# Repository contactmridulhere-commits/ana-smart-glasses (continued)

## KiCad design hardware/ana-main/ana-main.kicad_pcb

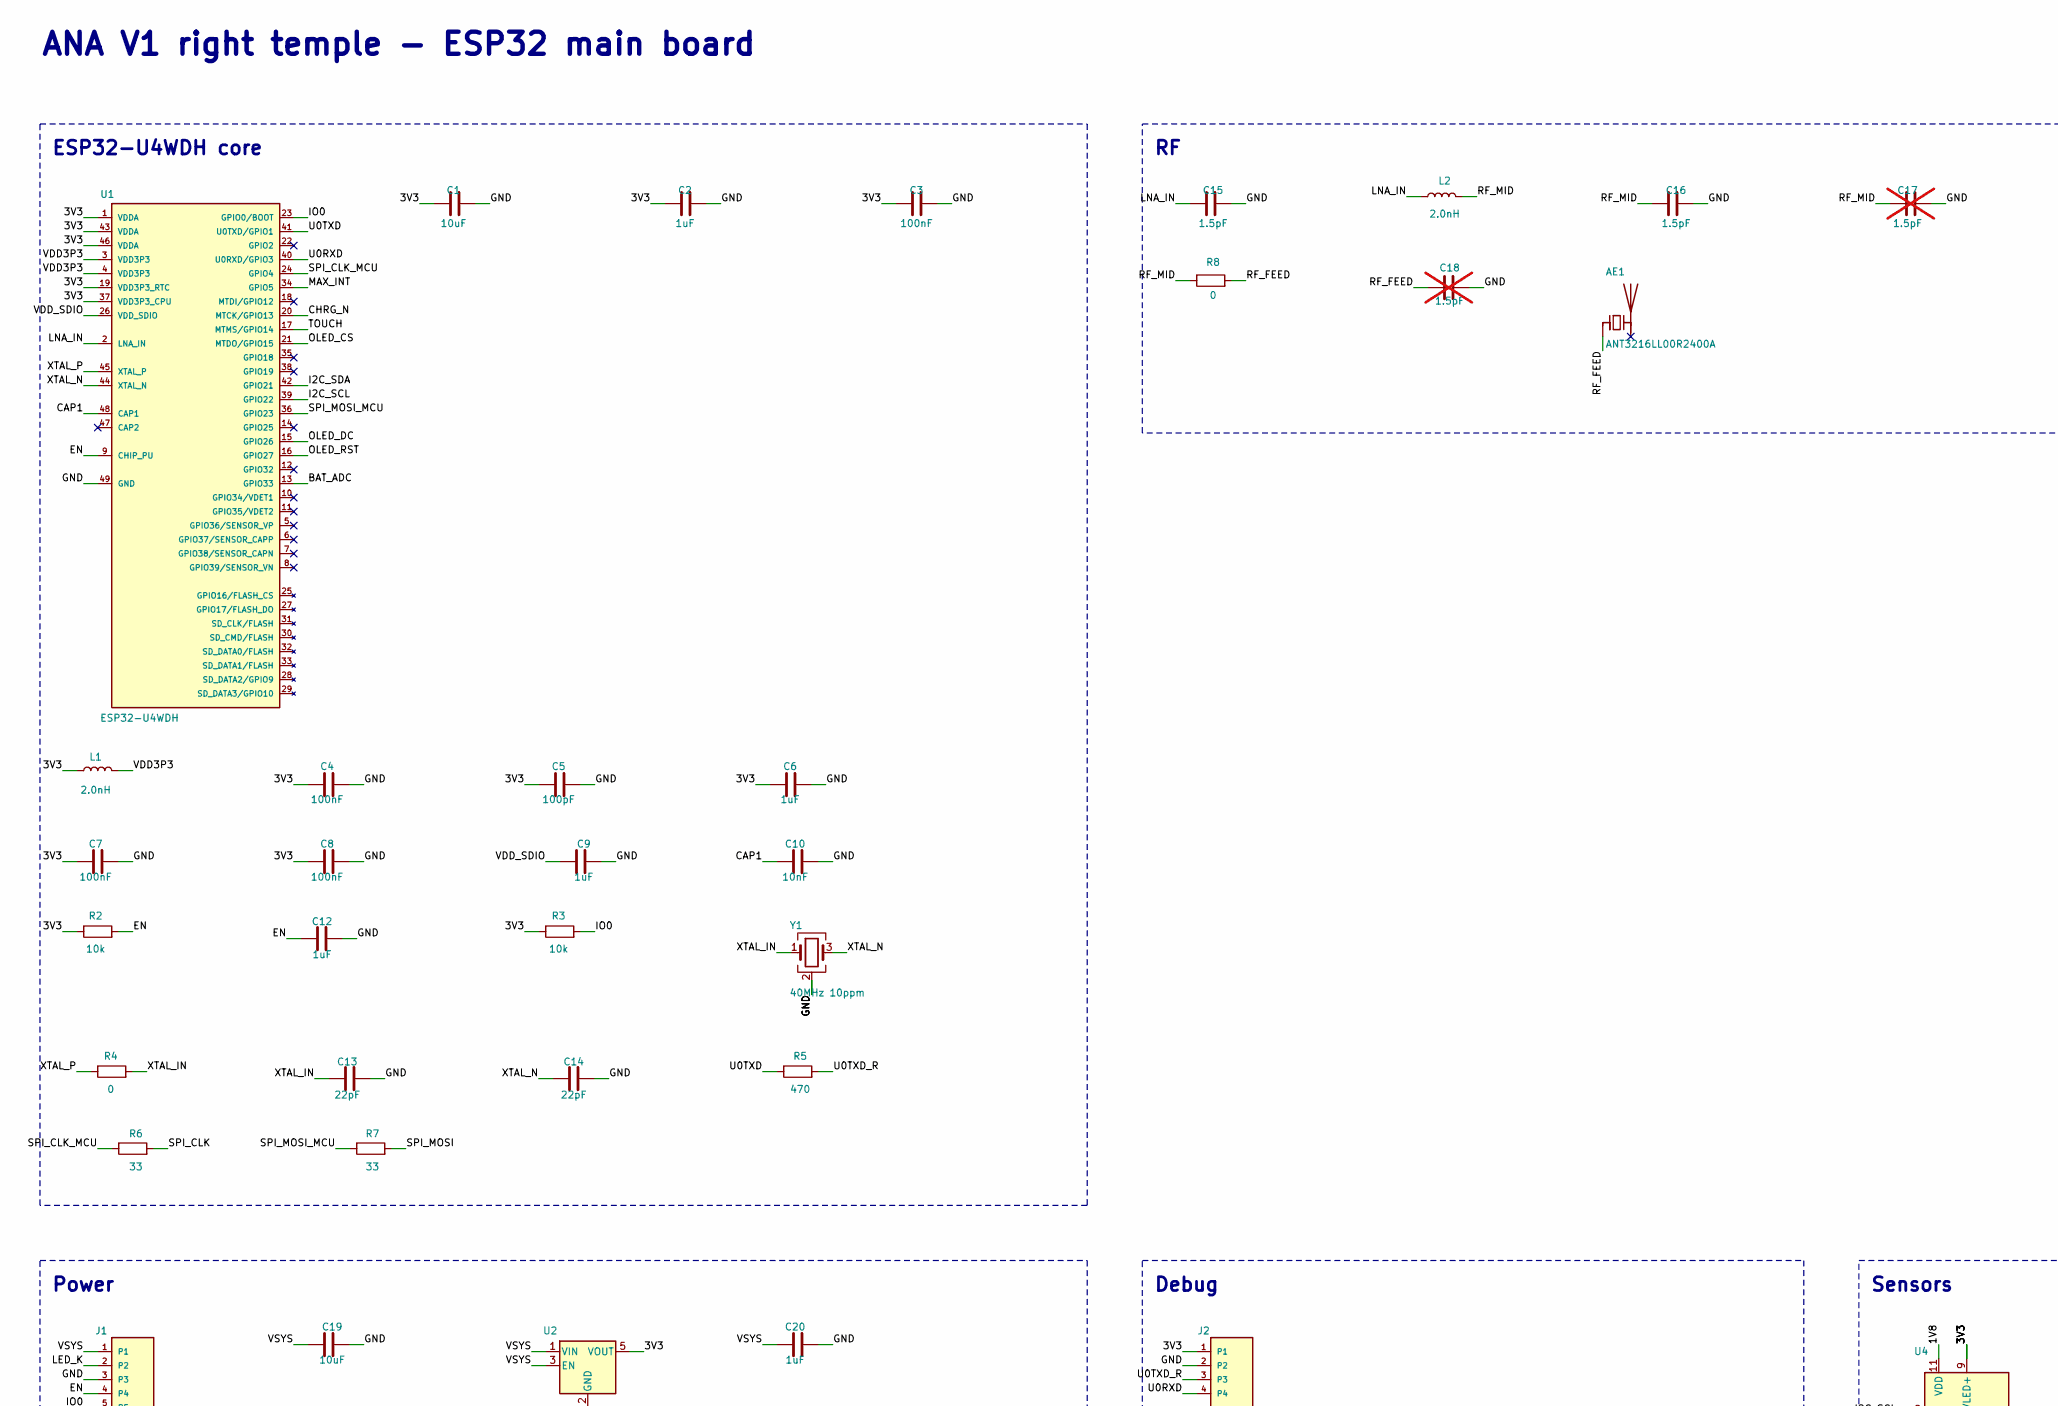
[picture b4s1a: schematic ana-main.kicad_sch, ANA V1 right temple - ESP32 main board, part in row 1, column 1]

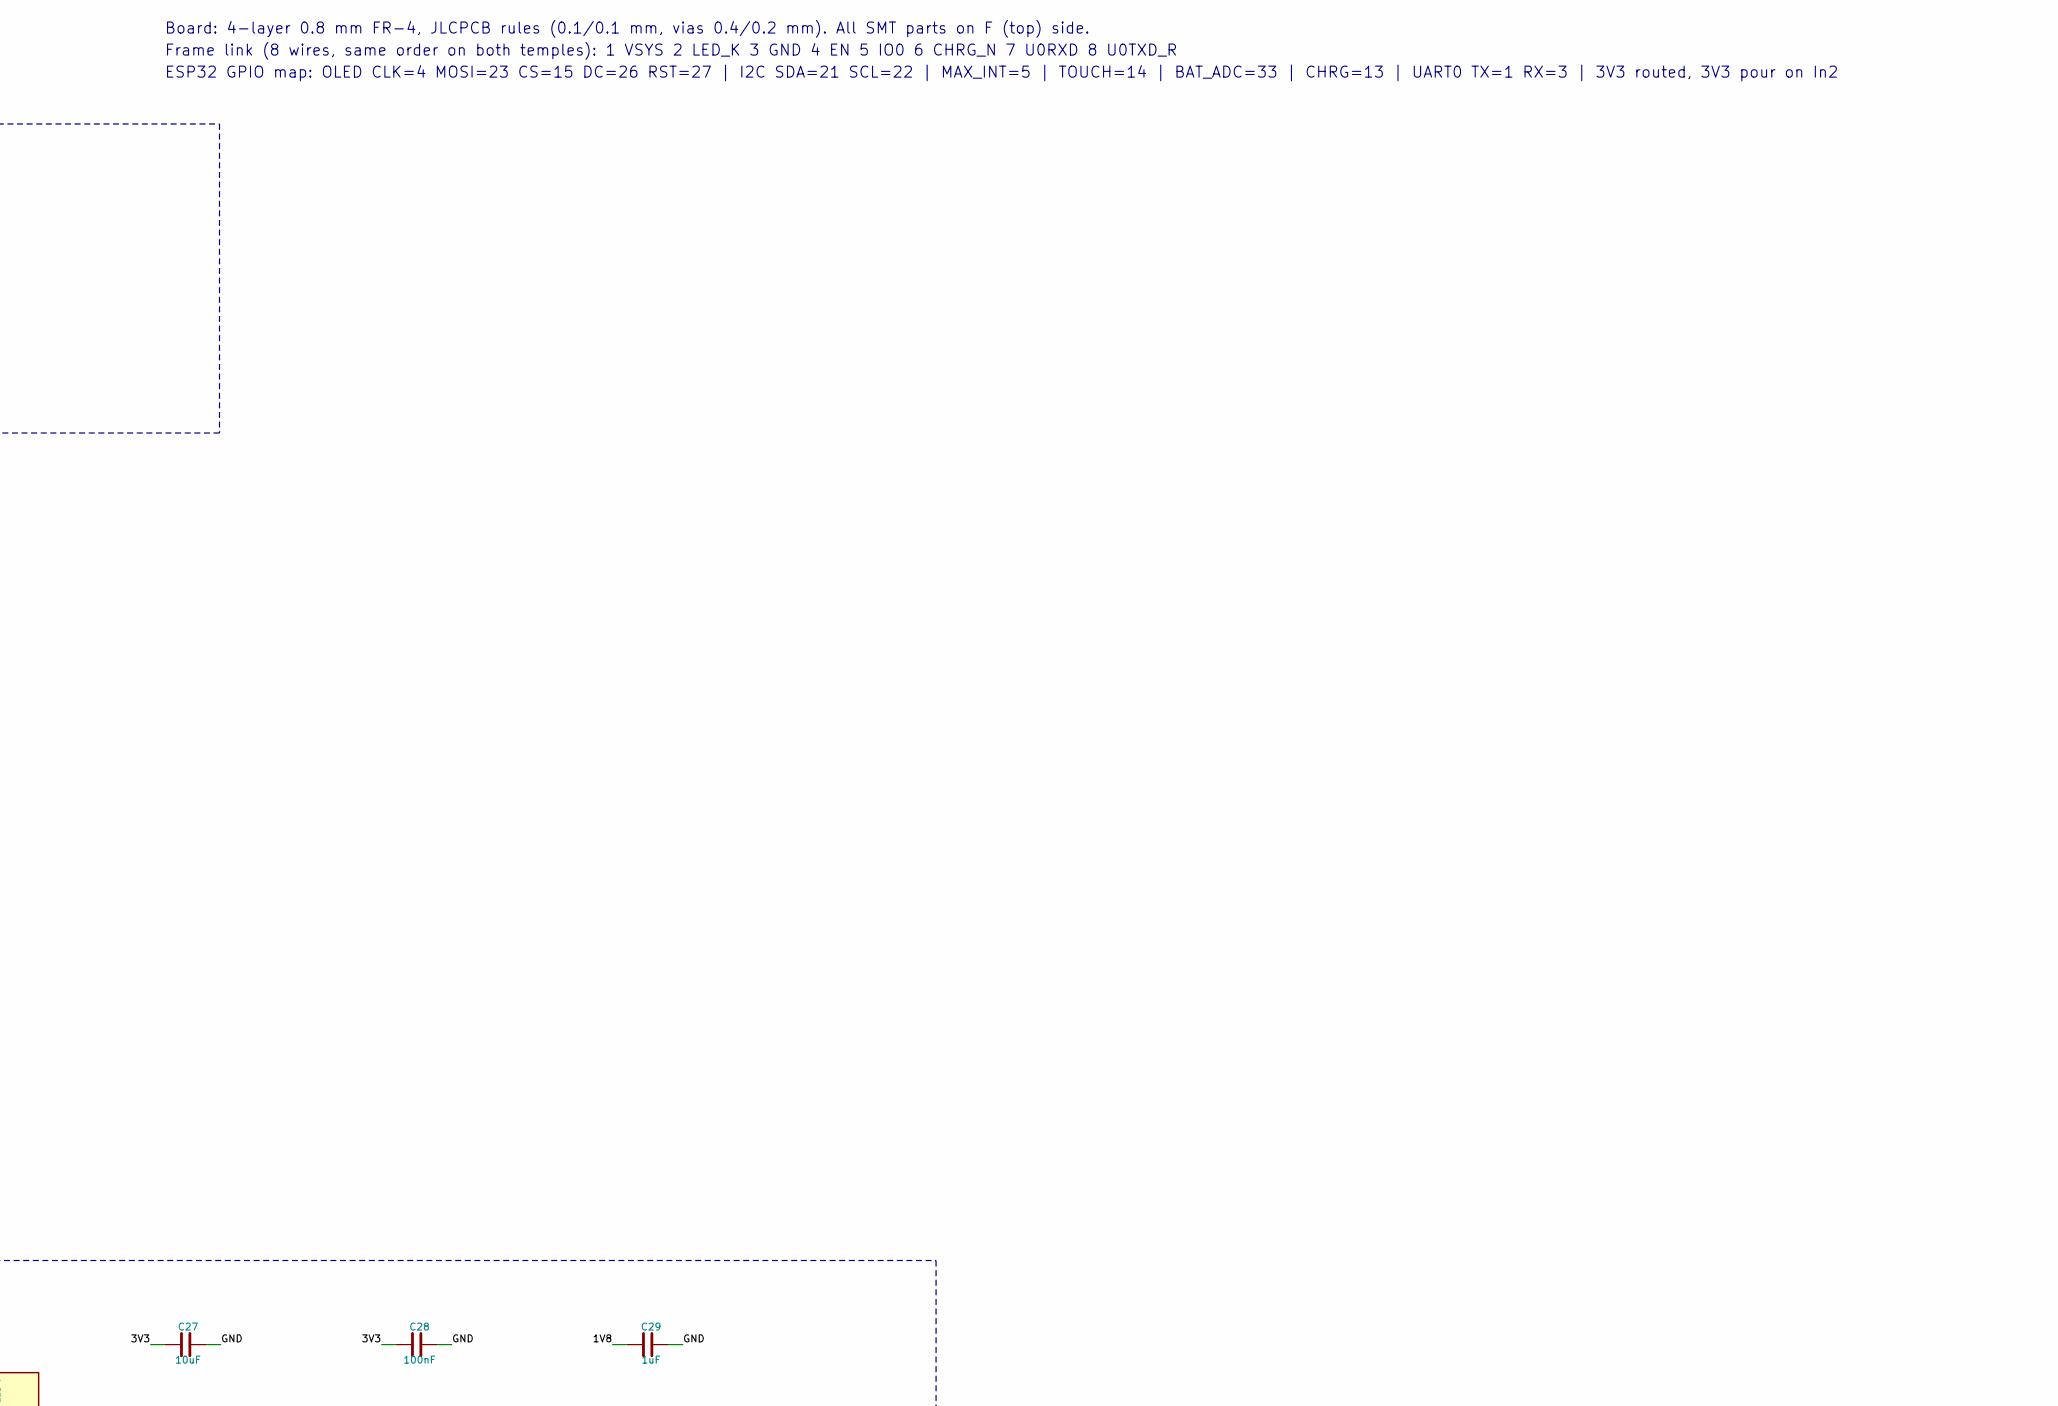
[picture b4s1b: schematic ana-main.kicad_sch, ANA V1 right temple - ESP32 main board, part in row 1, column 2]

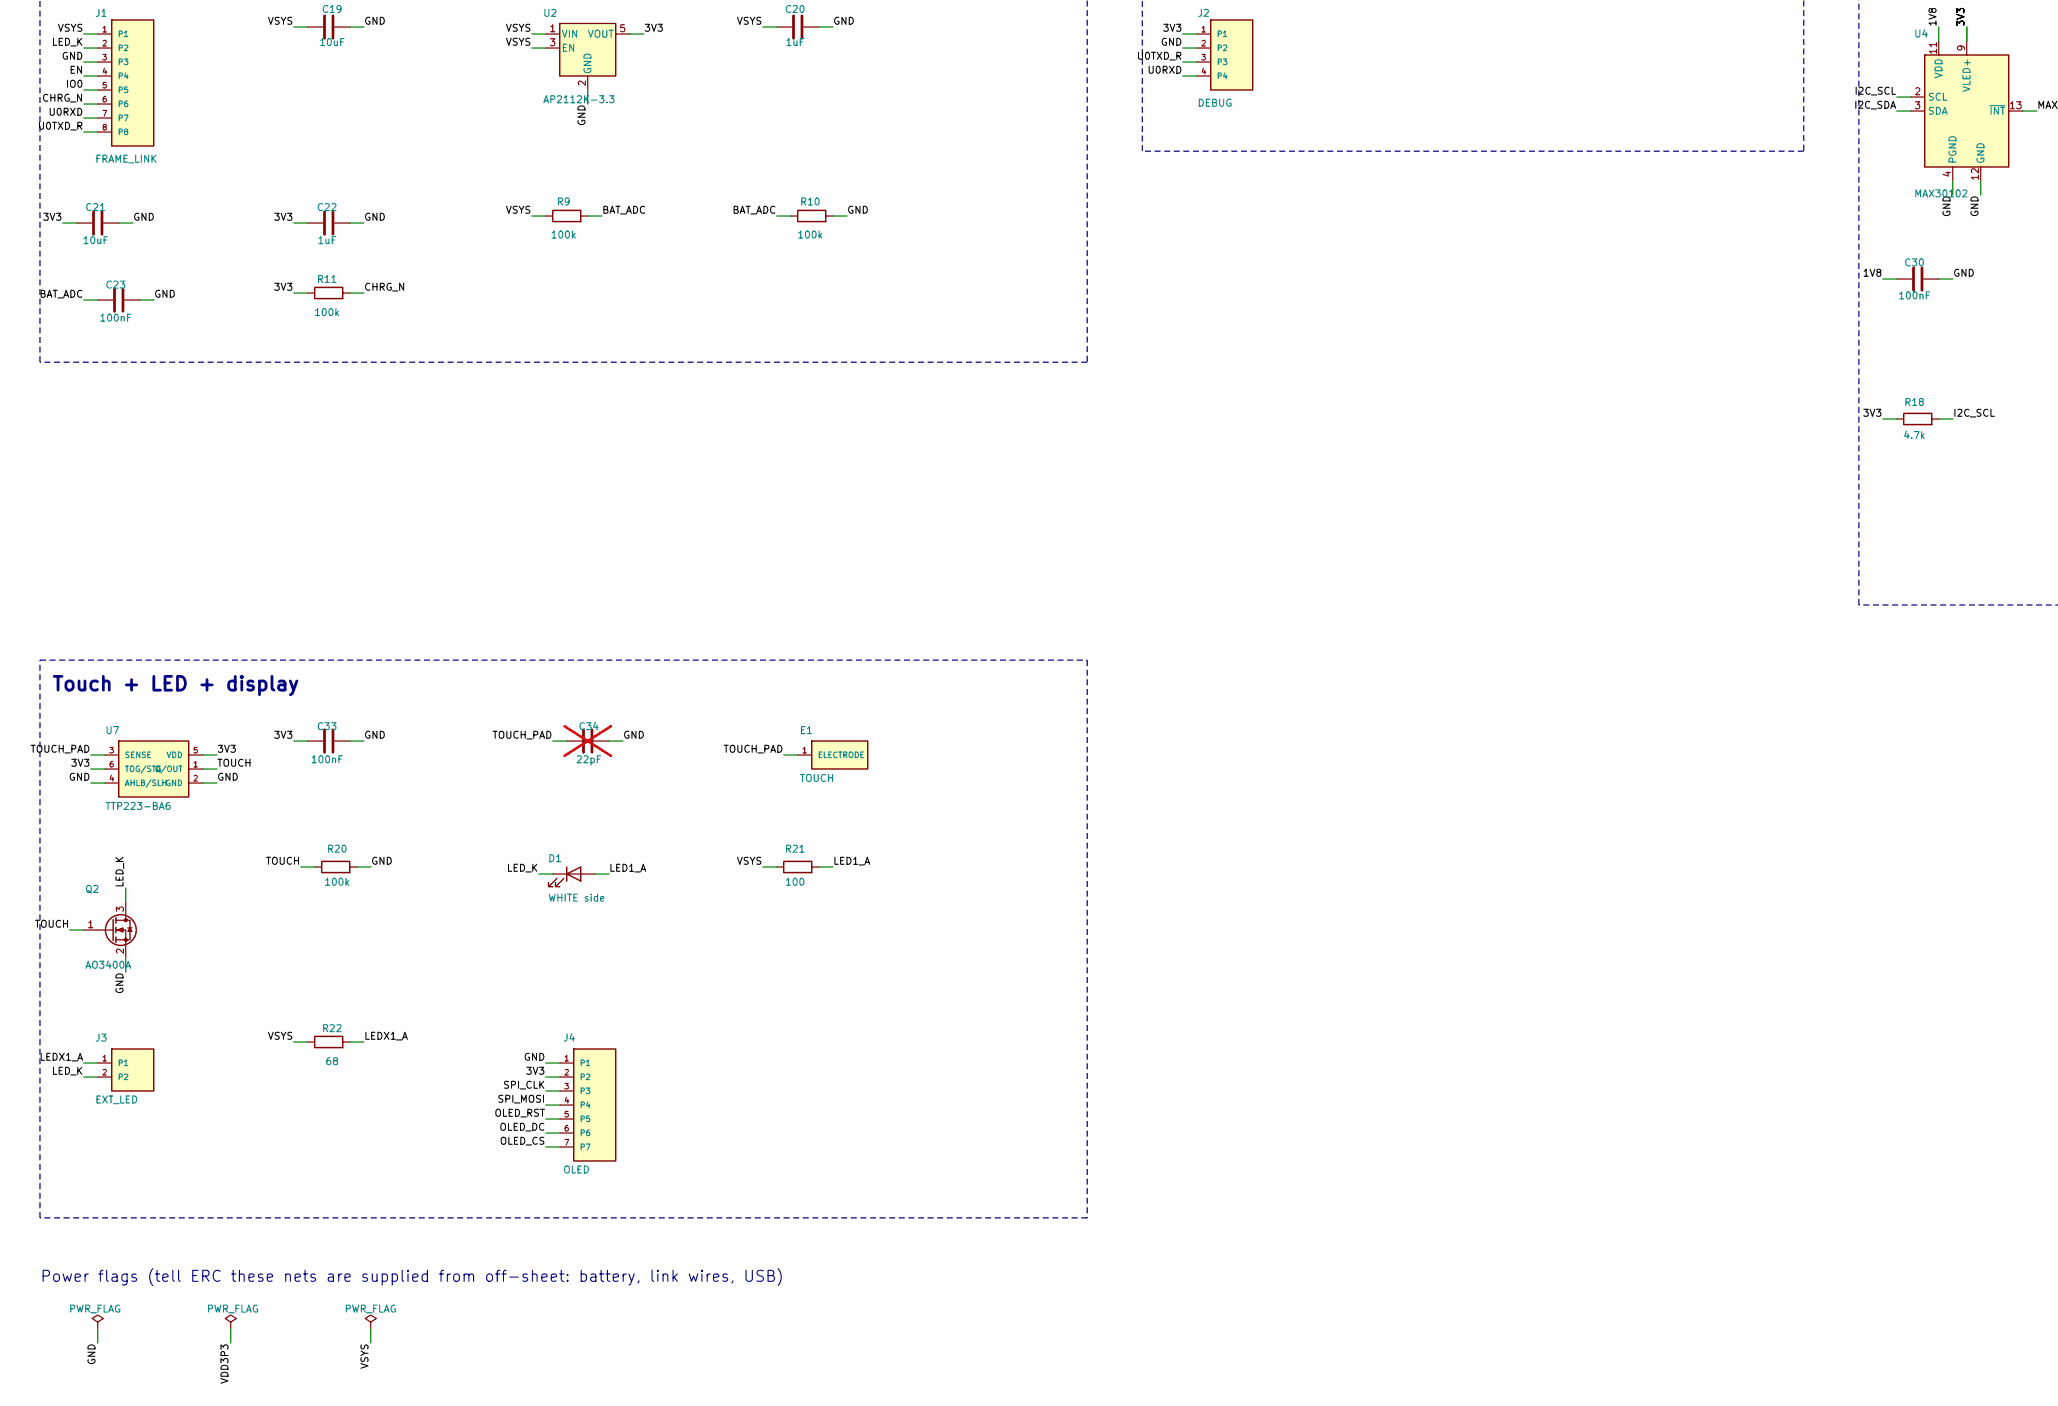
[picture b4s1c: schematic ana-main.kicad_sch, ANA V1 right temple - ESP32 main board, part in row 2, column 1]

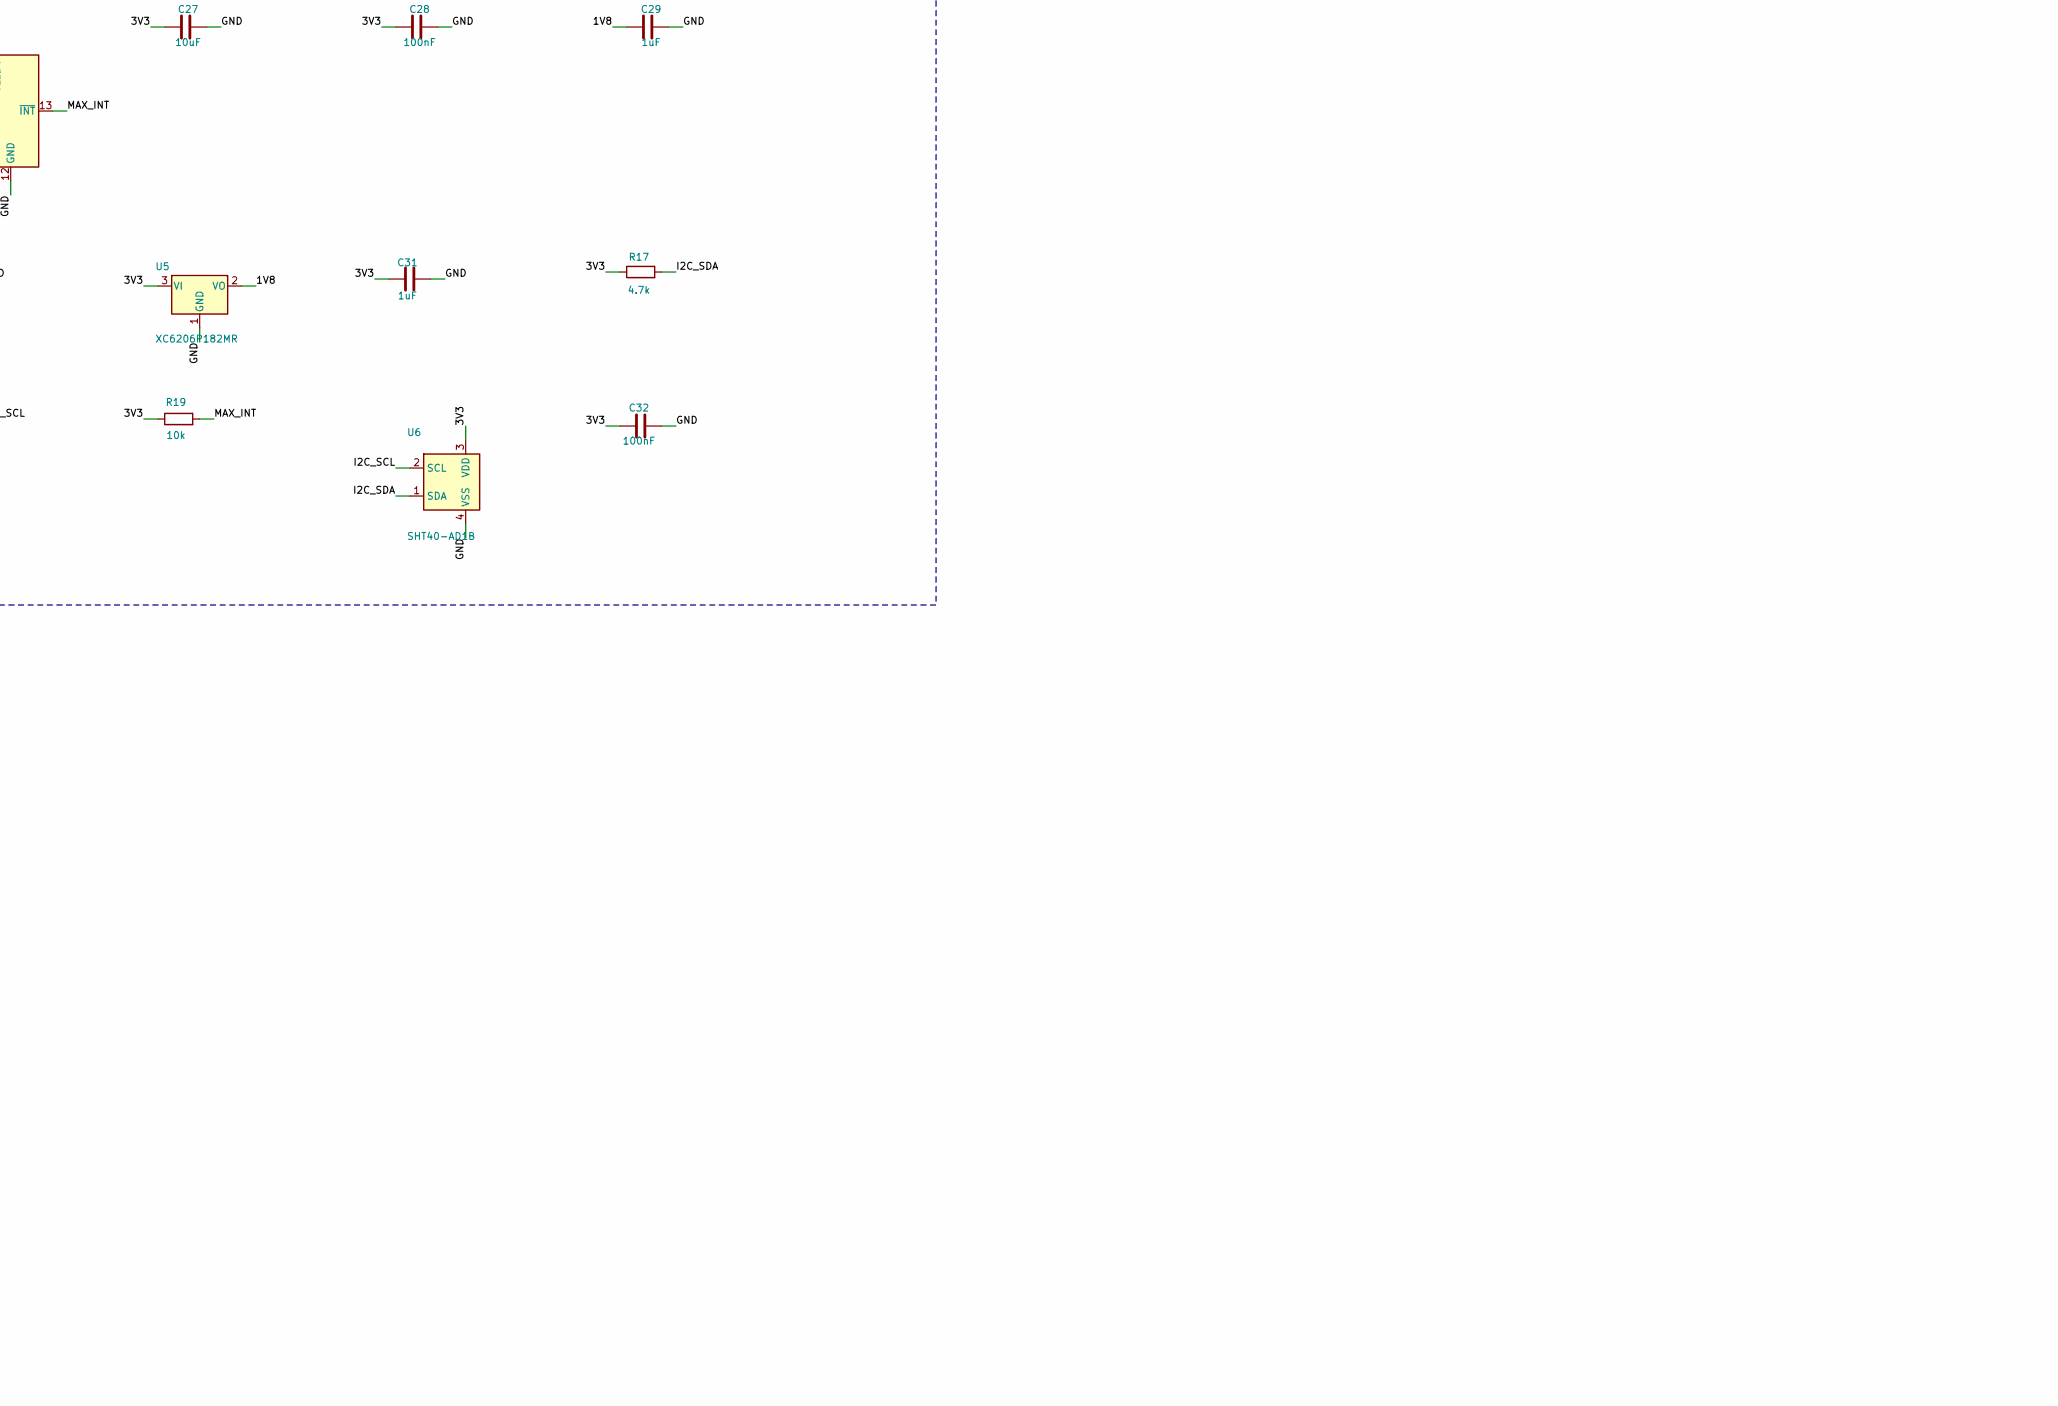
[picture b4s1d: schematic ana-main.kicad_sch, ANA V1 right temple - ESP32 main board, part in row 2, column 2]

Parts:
AE1: ANT3216LL00R2400A; ANT_Yageo_ANT3216LL00R2400A; MPN ANT3216LL00R2400A; LCSC C293767
C1, C21, C27: 10uF; C_0402_1005Metric; LCSC C15525
C2, C6, C9, C12, C20, C22, C29, C31: 1uF; C_0402_1005Metric; LCSC C52923
C3, C4, C7, C8, C23, C28, C30, C32, C33: 100nF; C_0402_1005Metric; LCSC C1525
C5: 100pF; C_0402_1005Metric; LCSC C1546
C10: 10nF; C_0402_1005Metric; LCSC C15195
C13, C14: 22pF; C_0402_1005Metric; LCSC C1555
C15, C16: 1.5pF; C_0402_1005Metric; LCSC C1552
C17, C18: 1.5pF; C_0402_1005Metric; LCSC C1552; not fitted
C19: 10uF; C_0603_1608Metric; LCSC C380317
C34: 22pF; C_0402_1005Metric; LCSC C1555; not fitted
D1: WHITE side; LED_SideView_1.6x0.75mm_YLED0602; MPN YLED0602WSIDE; LCSC C46635136
E1: TOUCH; TouchElectrode_4x10mm_Back
J1: FRAME_LINK; WirePads_1x08_P1.50mm
J2: DEBUG; TestPads_1x04_P1.10mm
J3: EXT_LED; WirePads_1x02_P1.50mm
J4: OLED; WirePads_1x07_P1.50mm
L1, L2: 2.0nH; L_0402_1005Metric; MPN MLG1005S2N0BT000; LCSC C76769
Q2: AO3400A; SOT-23; MPN AO3400A; LCSC C20917
R2, R3, R19: 10k; R_0402_1005Metric; LCSC C25744
R4, R8: 0; R_0402_1005Metric; LCSC C17168
R5: 470; R_0402_1005Metric; LCSC C25117
R6, R7: 33; R_0402_1005Metric; LCSC C25105
R9, R10, R11, R20: 100k; R_0402_1005Metric; LCSC C25741
R17, R18: 4.7k; R_0402_1005Metric; LCSC C25900
R21: 100; R_0402_1005Metric; LCSC C25076
R22: 68; R_0402_1005Metric; LCSC C25131
U1: ESP32-U4WDH; QFN-48-1EP_5x5mm_P0.35mm_EP3.7x3.7mm_ThermalVias_NoBottomPad; MPN ESP32-U4WDH; LCSC C20622217
U2: AP2112K-3.3; SOT-23-5; MPN AP2112K-3.3TRG1; LCSC C51118
U4: MAX30102; Maxim_OLGA-14_3.3x5.6mm_P0.8mm; MPN MAX30102EFD+T; LCSC C6454833
U5: XC6206P182MR; SOT-23; MPN XC6206P182MR; LCSC C21659
U6: SHT40-AD1B; Sensirion_DFN-4_1.5x1.5mm_P0.8mm_SHT4x_NoCentralPad; MPN SHT40-AD1B-R2; LCSC C2909890
U7: TTP223-BA6; SOT-23-6; MPN TTP223-BA6-TD; LCSC C42422127
Y1: 40MHz 10ppm; Crystal_SMD_3225-4Pin_3.2x2.5mm; MPN X322540MPB4SI; LCSC C9010

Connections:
/1V8: C29.1, C30.1, U4.11 (VDD), U5.2 (VO)
/3V3: C1.1, C2.1, C3.1, C4.1, C5.1, C6.1, C7.1, C8.1, C21.1, C22.1, C27.1, C28.1, C31.1, C32.1, C33.1, J2.1, J4.2, L1.1, R2.1, R3.1, R11.1, R17.1, R18.1, R19.1, U1.1 (VDDA), U1.19 (VDD3P3_RTC), U1.37 (VDD3P3_CPU), U1.43 (VDDA), U1.46 (VDDA), U2.5 (VOUT), U4.9 (VLED+), U4.10 (VLED+), U5.3 (VI), U6.3 (VDD), U7.5 (VDD), U7.6 (TOG/STG)
/BAT_ADC: C23.1, R9.2, R10.1, U1.13 (GPIO33)
/CAP1: C10.1, U1.48 (CAP1)
/CHRG_N: J1.6, R11.2, U1.20 (MTCK/GPIO13)
/EN: C12.1, J1.4, R2.2, U1.9 (CHIP_PU)
/GND: C1.2, C2.2, C3.2, C4.2, C5.2, C6.2, C7.2, C8.2, C9.2, C10.2, C12.2, C13.2, C14.2, C15.2, C16.2, C17.2, C18.2, C19.2, C20.2, C21.2, C22.2, C23.2, C27.2, C28.2, C29.2, C30.2, C31.2, C32.2, C33.2, C34.2, J1.3, J2.2, J4.1, Q2.2 (S), R10.2, R20.2, U1.49 (GND), U2.2 (GND), U4.4 (PGND), U4.12 (GND), U5.1 (GND), U6.4 (VSS), U7.2 (GND), U7.4 (AHLB/SLH), Y1.2 (G), Y1.4 (G)
/I2C_SCL: R18.2, U1.39 (GPIO22), U4.2 (SCL), U6.2 (SCL)
/I2C_SDA: R17.2, U1.42 (GPIO21), U4.3 (SDA), U6.1 (SDA)
/IO0: J1.5, R3.2, U1.23 (GPIO0/BOOT)
/LED1_A: D1.2 (A), R21.2
/LEDX1_A: J3.1, R22.2
/LED_K: D1.1 (K), J1.2, J3.2, Q2.3 (D)
/LNA_IN: C15.1, L2.1, U1.2 (LNA_IN)
/MAX_INT: R19.2, U1.34 (GPIO5), U4.13 (~INT)
/OLED_CS: J4.7, U1.21 (MTDO/GPIO15)
/OLED_DC: J4.6, U1.15 (GPIO26)
/OLED_RST: J4.5, U1.16 (GPIO27)
/RF_FEED: AE1.1 (FEED), C18.1, R8.2
/RF_MID: C16.1, C17.1, L2.2, R8.1
/SPI_CLK: J4.3, R6.2
/SPI_CLK_MCU: R6.1, U1.24 (GPIO4)
/SPI_MOSI: J4.4, R7.2
/SPI_MOSI_MCU: R7.1, U1.36 (GPIO23)
/TOUCH: Q2.1 (G), R20.1, U1.17 (MTMS/GPIO14), U7.1 (Q/OUT)
/TOUCH_PAD: C34.1, E1.1, U7.3 (SENSE)
/U0RXD: J1.7, J2.4, U1.40 (U0RXD/GPIO3)
/U0TXD: R5.1, U1.41 (U0TXD/GPIO1)
/U0TXD_R: J1.8, J2.3, R5.2
/VDD3P3: L1.2, U1.3 (VDD3P3), U1.4 (VDD3P3)
/VDD_SDIO: C9.1, U1.26 (VDD_SDIO)
/VSYS: C19.1, C20.1, J1.1, R9.1, R21.1, R22.1, U2.1 (VIN), U2.3 (EN)
/XTAL_IN: C13.1, R4.2, Y1.1
/XTAL_N: C14.1, U1.44 (XTAL_N), Y1.3
/XTAL_P: R4.1, U1.45 (XTAL_P)

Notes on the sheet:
ANA V1 right temple - ESP32 main board
Board: 4-layer 0.8 mm FR-4, JLCPCB rules (0.1/0.1 mm, vias 0.4/0.2 mm). All SMT parts on F (top) side.
Frame link (8 wires, same order on both temples): 1 VSYS 2 LED_K 3 GND 4 EN 5 IO0 6 CHRG_N 7 U0RXD 8 U0TXD_R
ESP32 GPIO map: OLED CLK=4 MOSI=23 CS=15 DC=26 RST=27 | I2C SDA=21 SCL=22 | MAX_INT=5 | TOUCH=14 | BAT_ADC=33 | CHRG=13 | UART0 TX=1 RX=3 | 3V3 routed, 3V3 pour on In2
ESP32-U4WDH core
Power
Debug
Sensors
Touch + LED + display
Power flags (tell ERC these nets are supplied from off-sheet: battery, link wires, USB)

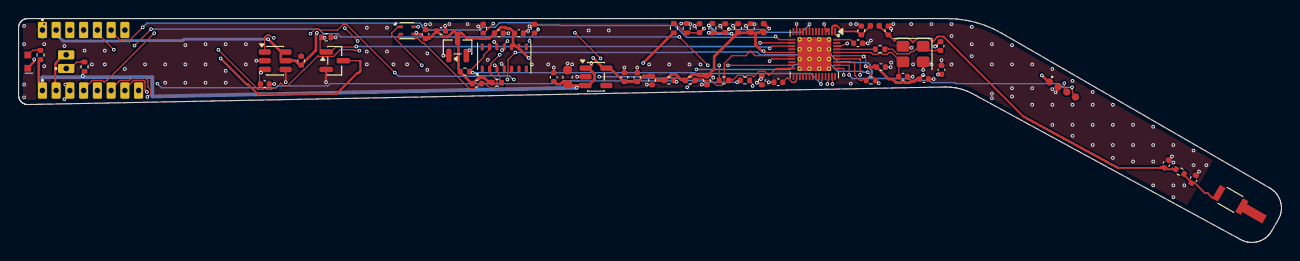
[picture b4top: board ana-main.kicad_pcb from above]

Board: 4 copper layers, 137.8 x 24.4 mm, 63 parts (1 on the bottom side), 35 nets.

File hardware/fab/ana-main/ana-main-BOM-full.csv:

Ref,Value,Footprint,LCSC,MPN,Fitted by,Note
U1,ESP32-U4WDH,ana:QFN-48-1EP_5x5mm_P0.35mm_EP3.7x3.7mm_ThermalVias_NoBottomPad,C20622217,ESP32-U4WDH,JLCPCB,"ESP32, 4 MB flash in package, BT Classic"
C1,10uF,Capacitor_SMD:C_0402_1005Metric,C15525,,JLCPCB,bulk at ESP32 supply entry
C2,1uF,Capacitor_SMD:C_0402_1005Metric,C52923,,JLCPCB,
C3,100nF,Capacitor_SMD:C_0402_1005Metric,C1525,,JLCPCB,
L1,2.0nH,Inductor_SMD:L_0402_1005Metric,C76769,MLG1005S2N0BT000,JLCPCB,VDD3P3 RF supply filter (Espressif ref.)
C4,100nF,Capacitor_SMD:C_0402_1005Metric,C1525,,JLCPCB,VDDA pin 1
C5,100pF,Capacitor_SMD:C_0402_1005Metric,C1546,,JLCPCB,VDDA pins 43/46
C6,1uF,Capacitor_SMD:C_0402_1005Metric,C52923,,JLCPCB,VDDA pins 43/46
C7,100nF,Capacitor_SMD:C_0402_1005Metric,C1525,,JLCPCB,VDD3P3_RTC pin 19
C8,100nF,Capacitor_SMD:C_0402_1005Metric,C1525,,JLCPCB,VDD3P3_CPU pin 37
C9,1uF,Capacitor_SMD:C_0402_1005Metric,C52923,,JLCPCB,VDD_SDIO (in-package flash supply)
C10,10nF,Capacitor_SMD:C_0402_1005Metric,C15195,,JLCPCB,"CAP1, 10% (required). The optional CAP2 RC (3.3nF || 20k) is omitted: Espressif allows this when deep sleep is not used"
R2,10k,Resistor_SMD:R_0402_1005Metric,C25744,,JLCPCB,CHIP_PU pull-up
C12,1uF,Capacitor_SMD:C_0402_1005Metric,C52923,,JLCPCB,CHIP_PU RC delay
R3,10k,Resistor_SMD:R_0402_1005Metric,C25744,,JLCPCB,GPIO0 boot strap pull-up
Y1,40MHz 10ppm,Crystal:Crystal_SMD_3225-4Pin_3.2x2.5mm,C9010,X322540MPB4SI,JLCPCB,"40 MHz +-10 ppm, CL 15 pF"
R4,0,Resistor_SMD:R_0402_1005Metric,C17168,,JLCPCB,series element on XTAL_P (tune after RF test)
C13,22pF,Capacitor_SMD:C_0402_1005Metric,C1555,,JLCPCB,crystal load
C14,22pF,Capacitor_SMD:C_0402_1005Metric,C1555,,JLCPCB,crystal load
R5,470,Resistor_SMD:R_0402_1005Metric,C25117,,JLCPCB,U0TXD harmonic suppression (Espressif ref. 499R)
R6,33,Resistor_SMD:R_0402_1005Metric,C25105,,JLCPCB,SPI clock series R
R7,33,Resistor_SMD:R_0402_1005Metric,C25105,,JLCPCB,SPI data series R
C15,1.5pF,Capacitor_SMD:C_0402_1005Metric,C1552,,JLCPCB,chip-side CLC match (tune)
L2,2.0nH,Inductor_SMD:L_0402_1005Metric,C76769,MLG1005S2N0BT000,JLCPCB,chip-side CLC match (tune)
C16,1.5pF,Capacitor_SMD:C_0402_1005Metric,C1552,,JLCPCB,chip-side CLC match (tune)
C17,1.5pF,Capacitor_SMD:C_0402_1005Metric,C1552,,DNP (tuning option),"antenna-side match, not fitted"
R8,0,Resistor_SMD:R_0402_1005Metric,C17168,,JLCPCB,antenna-side match series (0R or L)
C18,1.5pF,Capacitor_SMD:C_0402_1005Metric,C1552,,DNP (tuning option),"antenna-side match, not fitted"
AE1,ANT3216LL00R2400A,ana:ANT_Yageo_ANT3216LL00R2400A,C293767,ANT3216LL00R2400A,JLCPCB,2.4 GHz ceramic chip antenna at the ear-tip end
J1,FRAME_LINK,ana:WirePads_1x08_P1.50mm,,,you (wire/pad),8-wire link to left temple: VSYS LED_K GND EN IO0 CHRG RX TX
C19,10uF,Capacitor_SMD:C_0603_1608Metric,C380317,,JLCPCB,VSYS entry bulk
U2,AP2112K-3.3,Package_TO_SOT_SMD:SOT-23-5,C51118,AP2112K-3.3TRG1,JLCPCB,"3.3 V 600 mA LDO, 250 mV dropout"
C20,1uF,Capacitor_SMD:C_0402_1005Metric,C52923,,JLCPCB,
C21,10uF,Capacitor_SMD:C_0402_1005Metric,C15525,,JLCPCB,
C22,1uF,Capacitor_SMD:C_0402_1005Metric,C52923,,JLCPCB,
R9,100k,Resistor_SMD:R_0402_1005Metric,C25741,,JLCPCB,battery/VSYS divider
R10,100k,Resistor_SMD:R_0402_1005Metric,C25741,,JLCPCB,
C23,100nF,Capacitor_SMD:C_0402_1005Metric,C1525,,JLCPCB,ADC filter
R11,100k,Resistor_SMD:R_0402_1005Metric,C25741,,JLCPCB,charger status pull-up
J2,DEBUG,ana:TestPads_1x04_P1.10mm,,,you (wire/pad),bring-up pads on the ear tip: 3V3 GND TX (after R5) RX; EN and IO0 are on J1
U4,MAX30102,OptoDevice:Maxim_OLGA-14_3.3x5.6mm_P0.8mm,C6454833,MAX30102EFD+T,JLCPCB,"HR/SpO2, faces the skin (inner face)"
C27,10uF,Capacitor_SMD:C_0402_1005Metric,C15525,,JLCPCB,VLED+ bulk
C28,100nF,Capacitor_SMD:C_0402_1005Metric,C1525,,JLCPCB,VLED+
C29,1uF,Capacitor_SMD:C_0402_1005Metric,C52923,,JLCPCB,MAX30102 VDD
C30,100nF,Capacitor_SMD:C_0402_1005Metric,C1525,,JLCPCB,
U5,XC6206P182MR,Package_TO_SOT_SMD:SOT-23,C21659,XC6206P182MR,JLCPCB,1.8 V for MAX30102 core
C31,1uF,Capacitor_SMD:C_0402_1005Metric,C52923,,JLCPCB,
R17,4.7k,Resistor_SMD:R_0402_1005Metric,C25900,,JLCPCB,I2C pull-up
R18,4.7k,Resistor_SMD:R_0402_1005Metric,C25900,,JLCPCB,I2C pull-up
R19,10k,Resistor_SMD:R_0402_1005Metric,C25744,,JLCPCB,INT pull-up
U6,SHT40-AD1B,Sensor_Humidity:Sensirion_DFN-4_1.5x1.5mm_P0.8mm_SHT4x_NoCentralPad,C2909890,SHT40-AD1B-R2,JLCPCB,"temperature + humidity (replaces DHT11), I2C 0x44"
C32,100nF,Capacitor_SMD:C_0402_1005Metric,C1525,,JLCPCB,
U7,TTP223-BA6,Package_TO_SOT_SMD:SOT-23-6,C42422127,TTP223-BA6-TD,JLCPCB,"toggle mode, power-up low (like V1)"
C33,100nF,Capacitor_SMD:C_0402_1005Metric,C1525,,JLCPCB,
C34,22pF,Capacitor_SMD:C_0402_1005Metric,C1555,,DNP (tuning option),"touch sensitivity trim, fit 0-50 pF if needed"
E1,TOUCH,ana:TouchElectrode_4x10mm_Back,,,you (wire/pad),"electrode on outer copper, touch through the cover"
Q2,AO3400A,Package_TO_SOT_SMD:SOT-23,C20917,AO3400A,JLCPCB,low-side LED switch
R20,100k,Resistor_SMD:R_0402_1005Metric,C25741,,JLCPCB,gate pull-down while 3V3 ramps
D1,WHITE side,ana:LED_SideView_1.6x0.75mm_YLED0602,C46635136,YLED0602WSIDE,JLCPCB,side-emitting white LED at hinge end
R21,100,Resistor_SMD:R_0402_1005Metric,C25076,,JLCPCB,LED current ~5-15 mA
J3,EXT_LED,ana:WirePads_1x02_P1.50mm,,,you (wire/pad),optional external flashlight LED at the frame corner (+ / -)
R22,68,Resistor_SMD:R_0402_1005Metric,C25131,,JLCPCB,external LED current
J4,OLED,ana:WirePads_1x07_P1.50mm,,,you (wire/pad),to 7-pin SPI SSD1306 OLED module: GND VCC D0 D1 RES DC CS

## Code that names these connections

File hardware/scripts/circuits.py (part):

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from dataclasses import dataclass, field

LINK_ORDER = ['VSYS', 'LED_K', 'GND', 'EN', 'IO0', 'CHRG_N', 'U0RXD', 'U0TXD_R']
OLED_ORDER = ['GND', '3V3', 'SPI_CLK', 'SPI_MOSI', 'OLED_RST', 'OLED_DC', 'OLED_CS']  # 7-pin SPI OLED module order


@dataclass
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    #   pins 15-24 face the hinge end, 1-14 the top edge, 25-38 the bottom edge, 39-48 the ear tip.
    # Signals that travel to the hinge end use hinge-side / top-front pins (GPIO matrix routes SPI/I2C anywhere).
    # U4WDH: GPIO16/17 and SD_* are wired to the in-package flash -> left unconnected.
    # Straps: GPIO12 (MTDI) and GPIO2 left free; GPIO15 (MTDO) drives OLED CS (idle high, fine at boot).
    esp = {
        '1': '3V3', '43': '3V3', '46': '3V3', '19': '3V3', '37': '3V3',
        '3': 'VDD3P3', '4': 'VDD3P3', '26': 'VDD_SDIO',
        '2': 'LNA_IN', '45': 'XTAL_P', '44': 'XTAL_N', '48': 'CAP1', '47': None, '9': 'EN', '49': 'GND',
        '23': 'IO0', '41': 'U0TXD', '40': 'U0RXD',
        '15': 'OLED_DC',        # GPIO26  (hinge-facing side)
        '16': 'OLED_RST',       # GPIO27
        '17': 'TOUCH',          # GPIO14 (RTC GPIO, can wake from deep sleep)
        '20': 'CHRG_N',         # GPIO13
        '21': 'OLED_CS',        # GPIO15 (MTDO strap; CS idles high)
        '24': 'SPI_CLK_MCU',    # GPIO4  -> OLED D0
        '13': 'BAT_ADC',        # GPIO33 ADC1_CH5 (top edge, next to the hinge-side corner)
        '34': 'MAX_INT',        # GPIO5  (open-drain INT, 10k pull-up keeps the strap high at boot)
        '36': 'SPI_MOSI_MCU',   # GPIO23 (VSPI MOSI) -> OLED D1
        '39': 'I2C_SCL',        # GPIO22 (same I2C pins as V1)
        '42': 'I2C_SDA',        # GPIO21
        '5': None, '6': None, '7': None, '8': None, '10': None, '11': None, '12': None, '14': None, '18': None,
        '35': None, '22': None, '38': None, '25': None, '27': None, '28': None, '29': None, '30': None, '31': None,
        '32': None, '33': None,
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        C('C10', '10nF', 'CAP1', 'GND', B, 'CAP1, 10% (required). The optional CAP2 RC (3.3nF || 20k) is omitted: '
          'Espressif allows this when deep sleep is not used'),
        R('R2', '10k', '3V3', 'EN', B, 'CHIP_PU pull-up'), C('C12', '1uF', 'EN', 'GND', B, 'CHIP_PU RC delay'),
        R('R3', '10k', '3V3', 'IO0', B, 'GPIO0 boot strap pull-up'),
        Comp('Y1', 'Device:Crystal_GND24', '40MHz 10ppm', 'Crystal:Crystal_SMD_3225-4Pin_3.2x2.5mm',
             {'1': 'XTAL_IN', '2': 'GND', '3': 'XTAL_N', '4': 'GND'}, 'C9010', 'X322540MPB4SI', block=B,
             desc='40 MHz +-10 ppm, CL 15 pF'),
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    c += [
        Comp('U4', 'Interface_USB:CP2102N-Axx-xQFN24', 'CP2102N-A02-GQFN24', 'ana:QFN-24-1EP_4x4mm_P0.5mm_EP2.6x2.6mm_ThermalVias_NoBottomPad',
             cp, 'C969151', 'CP2102N-A02-GQFN24R', block=B,
             desc='USB-UART; on whenever the glasses are on (own 3.3 V regulator from VSYS), so its pins never '
                  'back-power the ESP32'),
        C('C8', '1uF', 'VSYS', 'GND', B, 'VREGIN'), C('C9', '1uF', 'CP_3V3', 'GND', B, 'VDD (regulator out)'),
        C('C10', '100nF', 'CP_3V3', 'GND', B, 'VDD / VIO'),
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
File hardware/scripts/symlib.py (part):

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        ('49', 'GND', 'power_in'),
    ]
    right = [
        ('23', 'GPIO0/BOOT', 'bidirectional'), ('41', 'U0TXD/GPIO1', 'bidirectional'),
        ('22', 'GPIO2', 'bidirectional'), ('40', 'U0RXD/GPIO3', 'bidirectional'),
        ('24', 'GPIO4', 'bidirectional'), ('34', 'GPIO5', 'bidirectional'),
        ('18', 'MTDI/GPIO12', 'bidirectional'), ('20', 'MTCK/GPIO13', 'bidirectional'),
        ('17', 'MTMS/GPIO14', 'bidirectional'), ('21', 'MTDO/GPIO15', 'bidirectional'),
        ('35', 'GPIO18', 'bidirectional'), ('38', 'GPIO19', 'bidirectional'),
        ('42', 'GPIO21', 'bidirectional'), ('39', 'GPIO22', 'bidirectional'),
        ('36', 'GPIO23', 'bidirectional'), ('14', 'GPIO25', 'bidirectional'),
        ('15', 'GPIO26', 'bidirectional'), ('16', 'GPIO27', 'bidirectional'),
        ('12', 'GPIO32', 'bidirectional'), ('13', 'GPIO33', 'bidirectional'),
        ('10', 'GPIO34/VDET1', 'input'), ('11', 'GPIO35/VDET2', 'input'),
        ('5', 'GPIO36/SENSOR_VP', 'input'), ('6', 'GPIO37/SENSOR_CAPP', 'input'),
        ('7', 'GPIO38/SENSOR_CAPN', 'input'), ('8', 'GPIO39/SENSOR_VN', 'input'),
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                           [('4', 'G2', 'input'), ('3', 'S2', 'passive'), ('5', 'D12', 'passive')],
                           ref='Q', width=10.16, footprint='Package_TO_SOT_SMD:SOT-23-6',
                           desc='Dual N-MOSFET with common drain for Li-ion protection'))
    # TTP223 single-key capacitive touch (TTP223-BA6 / TTP223-BA6-TD pinout)
    syms.append(box_symbol('TTP223', [('3', 'SENSE', 'input'), ('6', 'TOG/STG', 'input'),
                                      ('4', 'AHLB/SLH', 'input')],
                           [('5', 'VDD', 'power_in'), ('1', 'Q/OUT', 'output'), ('2', 'GND', 'power_in')],
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
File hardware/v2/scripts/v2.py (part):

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# the temple harness: two rows of 8 wire holes, same pad order on the temple and on the pod
LINK_A = ['5V', 'GND', 'SDA', 'SCL', 'IMU_INT', 'PPG_INT', 'TOUCH', 'IR_PWM']
LINK_B = ['5V', 'GND', 'I2S_BCLK', 'I2S_LRCLK', 'MIC_SD', 'SPK_SD', 'GND', 'LED_PWM']
PI_A = ['SDA', 'SCL', 'IMU_INT', 'PPG_INT', 'TOUCH', 'IR_PWM', 'LED_PWM', 'GND']          # GPIO 2 3 4 5 17 12 13
PI_B = ['I2S_BCLK', 'I2S_LRCLK', 'MIC_SD', 'SPK_SD', 'HUB_TX', 'HUB_RX', 'PI_SHDN', 'GND']  # GPIO 18 19 20 21 15 14 6
ELECTRODES = ['E1', 'E2', 'E3', 'E4', 'E_REF', 'E_BIAS', 'GND']
C22 = dict(fp=FP_C0603, lcsc='C109448')

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    ads.update({'16': 'IN1P', '14': 'IN2P', '12': 'IN3P', '10': 'IN4P', '17': 'SRB1', '24': 'VREFP', '28': 'VCAP1',
                '30': 'VCAP2', '55': 'VCAP3', '26': 'VCAP4', '34': 'EEG_MOSI', '35': 'EEG_PWDN', '36': 'EEG_RST',
                '37': 'EEG_CLK', '38': 'EEG_START', '39': 'EEG_CS', '40': 'EEG_SCLK', '43': 'EEG_MISO',
                '47': 'EEG_DRDY', '42': 'EEG_GPIO', '44': 'EEG_GPIO', '45': 'EEG_GPIO', '46': 'EEG_GPIO',
                '60': 'BIASREF', '61': 'BIASINV', '63': 'BIASOUT'})
    c += [Comp('U3', 'Analog_ADC:ADS1299', 'ADS1299-4', 'Package_QFP:TQFP-64_10x10mm_P0.5mm', ads, 'C2651574',
               'ADS1299-4PAGR', block=B, desc='4-channel 24-bit EEG front end; inputs 1-4 against the reference on SRB1'),
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    for i in range(5):                                               # VCAP1: 100 uF (datasheet) = 5 x 22 uF
        c.append(Comp('C%d' % (23 + i), 'Device:C', '22uF', C22['fp'], {'1': 'VCAP1', '2': 'GND'}, C22['lcsc'], '',
                      False, B, 'VCAP1, 5 x 22 uF' if i == 0 else ''))
    c += [R('R12', '10k', 'EEG_GPIO', 'GND', B, 'unused GPIO1-4'), R('R13', '10k', 'EEG_CLK', 'GND', B, 'CLK unused'),
          R('R14', '10k', '3V3', 'EEG_PWDN', B), R('R15', '10k', '3V3', 'EEG_RST', B),
          R('R16', '100k', 'AVDD', 'BIASREF', B, 'mid-supply bias reference'), R('R17', '100k', 'BIASREF', 'GND', B),
          C('C28', '100nF', 'BIASREF', 'GND', B),
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    'Board: 4-layer 0.8 mm FR-4, JLCPCB rules (0.1/0.1 mm, vias 0.4/0.2 mm). All SMT parts on F (top) side.',
    'Temple harness (two rows of 8 wires, same order on temple and pod): A = ' + ' '.join(LINK_A) + ' | B = ' +
    ' '.join(LINK_B),
    'Pi GPIO: SDA 2, SCL 3, IMU_INT 4, PPG_INT 5, PI_SHDN 6, IR_PWM 12, LED_PWM 13, HUB_RX 14 (Pi TXD), HUB_TX 15 '
    '(Pi RXD), TOUCH 17, I2S BCLK 18, LRCLK 19, MIC_SD 20, SPK_SD 21',
]

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
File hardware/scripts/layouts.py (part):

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    # to put every pad centre exactly on the 0.05 mm routing grid.
    bb.place('U1', 86.825, 3.875, 270)
    bb.place('Y1', 97.6, 3.875, 180)                   # crystal on the ear-tip side (pins 44/45 face it)
    # 0R in XTAL_P, in line with pin 45; XTAL_N (pin 44) dips under it to the crystal's lower-left pad and
    # XTAL_IN passes between the crystal's pads to its upper-right pad
    bb.place('R4', 94.0, 3.35, 0)
    bb.place('C13', 100.6, 3.0, 90)                    # XTAL_IN load cap, right of the crystal (pad 1 below)
    bb.place('C14', 96.5, 6.35, 0)                     # XTAL_N load cap, under the crystal's lower-left pad
    bb.place('C10', 91.6, 2.7, 0)                      # CAP1, right of pin 48 (above the XTAL lines)
    bb.place('R5', 93.0, 6.75, 0)                      # U0TXD series R, next to pin 41's escape via
    bb.place('C9', 82.9, 6.95, 180)                    # VDD_SDIO, below the ESP32's bottom-left corner
    # antenna at the ear-tip end, along the tip axis
    s_ant = t.Lt - 1.0 - 4.6
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        x, y = bb.pad_pos(*a)
        bb.autoplace(ref, (x, y), rots=rots, **kw)

    # RF chain in a straight line along the top edge, right of the ESP32 (LNA_IN = pin 2 at the top-right)
    bb.place('C15', 91.95, 1.3, 90)      # shunt at LNA_IN (pad 1 on the RF line)
    bb.place('L2', 93.42, 0.8, 0)        # series
    bb.place('C16', 94.9, 1.3, 90)       # shunt at RF_MID
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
